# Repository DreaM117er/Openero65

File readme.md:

# OpeNero65

## 一、開發者前言

OpeNero65是我設計的第一把`ANSI配列`鍵盤，使用市面上都能輕易買到的RP2040開發板驅動，支援`QMK`/`VIAL`、多配列支持、階梯CapsLock等。本以為標準鍵盤外殼很好設計，後來發現單件CNC的價格過高，才改用堆疊外殼的設計方式，本次成品會採用3mm厚度壓克力製成。

OpeNero65 is the first `ANSI keyboard` I designed, it is driven by the RP2040 development board which can be easily purchased in the market, and it supports `QMK`/`VIAL`, multi-compatibility support, and ladder CapsLock, etc. Originally, I thought the standard keyboard case is very easy to design, then I found that the price of a single CNC is too high, so I switched to the stacked case design. Originally thought the standard keyboard case is very good design, but later found that the price of a single piece of CNC is too high, and then changed to the stacked case design, the finished product will be made of 3mm thickness acrylic.

設計堆疊殼也相當不輕鬆，特別是PCB階段它有一端是向外突起，接著開發板採用的是排針焊接固定，大大增加堆疊外殼的3D設計困難。仰角以堆疊外殼來說仰角有2種設計方式，但因為開發板固定在PCB上會有立體干涉存在，只能採用橫向堆疊的方式設計... 總體來說也經過一段時間折騰才順利完成。

The design of the stacked case is not easy, especially at the PCB stage it has an end that protrudes outward, and then the development board is fixed with rows of pins, which greatly increases the difficulty of the 3D design of the stacked case. Elevation angle to stack the case of the elevation angle of two design methods, but because the development board fixed on the PCB will have three-dimensional interference exists, can only be used in a horizontal stacking design... Overall, also after a period of time to successfully complete.

## 二、設計圖預覽

|||
|---|---|
|||
|||
|||

## 三、材料及使用工具

### A、材料：

|名稱|數量|備註|
|---|---|---|
|OpeNero65電路板（`PCB`）|1片|-|
|堆疊外殼（Stacking Case）|1組|10片堆疊材料|
|微控制器（`MCU`）|1片|`RP2040Supermini`、`RP2040Zero`|
|公母圓排針（M/F Pin header）|`9pin`、`5pin`|選配（`Optional`）|
|熱插拔座（Hotswap Sockets）|72個|`MX`規格（for MX switches）|
|`M2x5mm` 扁頭螺絲（Screws）|30根|-|
|`M2x4mm` 扁頭螺絲（Screws）|8根|-|
|`M2x3mm` 扁頭螺絲（Screws）|20根|-|
|`M2x18mm` 雙通銅柱（Spacer）|2根|-|
|`M2x12mm` 雙通銅柱（Spacer）|10根|-|
|`M2x5mm` 雙通銅柱（Spacer）|11根|-|
|`M2x3mm` 雙通銅柱（Spacer）|8根|-|
|`PCB`衛星軸（Stablizers）|3+1組|`2u`、`6.25u`/`7u`|
|衛星軸用潤滑酯|-|`Permatex 22058`/`81150`或`XHT-BDZ`|
|防滑腳貼（Rubber feets）|5個|高度隨個人而定|
|外徑`5mm` 內徑`2mm` 橡膠圈（Outer `ø5mm`, inner `ø2mm` O-rings）|15個|選配（`Optional`）|
|`M2` 防滑墊片（`M2` washers）|5個|選配（`Optional`）|

### B、使用工具：

- 電烙鐵及相關工具組（Solder gun and other packs）。
- 精密螺絲起子組（Screwdriver set）。
- 防靜電金屬鑷子（Anti-static metal tweezers）。
- 拔鍵器（Keycaps puller）。
- 拔軸器（Keyswitch puller）。
- 細毛毛刷（Brushes for stablizers）。

### C、注意事項：

> **Warning**
>
> 使用電烙鐵時注意用電、用火安全，環境通風。
> 
> Be carefull on fire and electricity safety when soldering in environmental ventilation.

> **Warning**
>
> 定製外殼前務必瞭解自身需求的鍵盤佈局（例如6.25u、7.00u Spacebar；WK、WKL等）。
> 
> Please understood which keyboard layout you need before making/ordering case. (ex: 6.25u, 7.00u spacebar; WK, WKL...)

> **Warning**
>
> 在定製製作Openero65外殼之前一定要特別注意，壓克力板一定會有`0.1-0.35mm`左右的公差存在，成品會比實際用計算機計算來的小一些。
> 
> Before you oeder cases from factory, arcylic boards must exist tolerances about `0.1-0.35mm`, the finished product will be smaller than the actual calculator.

> **Warning**
>
> 請準備個人喜歡的MX鍵軸65-66顆，以及調整衛星軸鋼絲的前置動作。
> 
> Please prepare 65-66 personal MX switches and adjusted stablizer wires before building keyboard.

材料及工具準備好之後，點我前往[組裝說明](guide.md)。

## 四、參考及使用資料
- [QMK Firmware](https://qmk.fm/).
- [VIAL](https://get.vial.today/).
- [KiCAD](https://www.kicad.org/) version `7.0.5.`
- [JLCPCB](https://jlcpcb.com/).
- [DeepL](https://www.deepl.com/translator).
- [AutoDesk Fusion360](https://www.autodesk.com/products/fusion-360/free-trial).
- Taiwan [Tatung University](https://www.ttu.edu.tw/) - [Department of Mechanical and Materials Engineering](https://mme.ttu.edu.tw/)
- And my friend: [YCT](https://github.com/yct38)

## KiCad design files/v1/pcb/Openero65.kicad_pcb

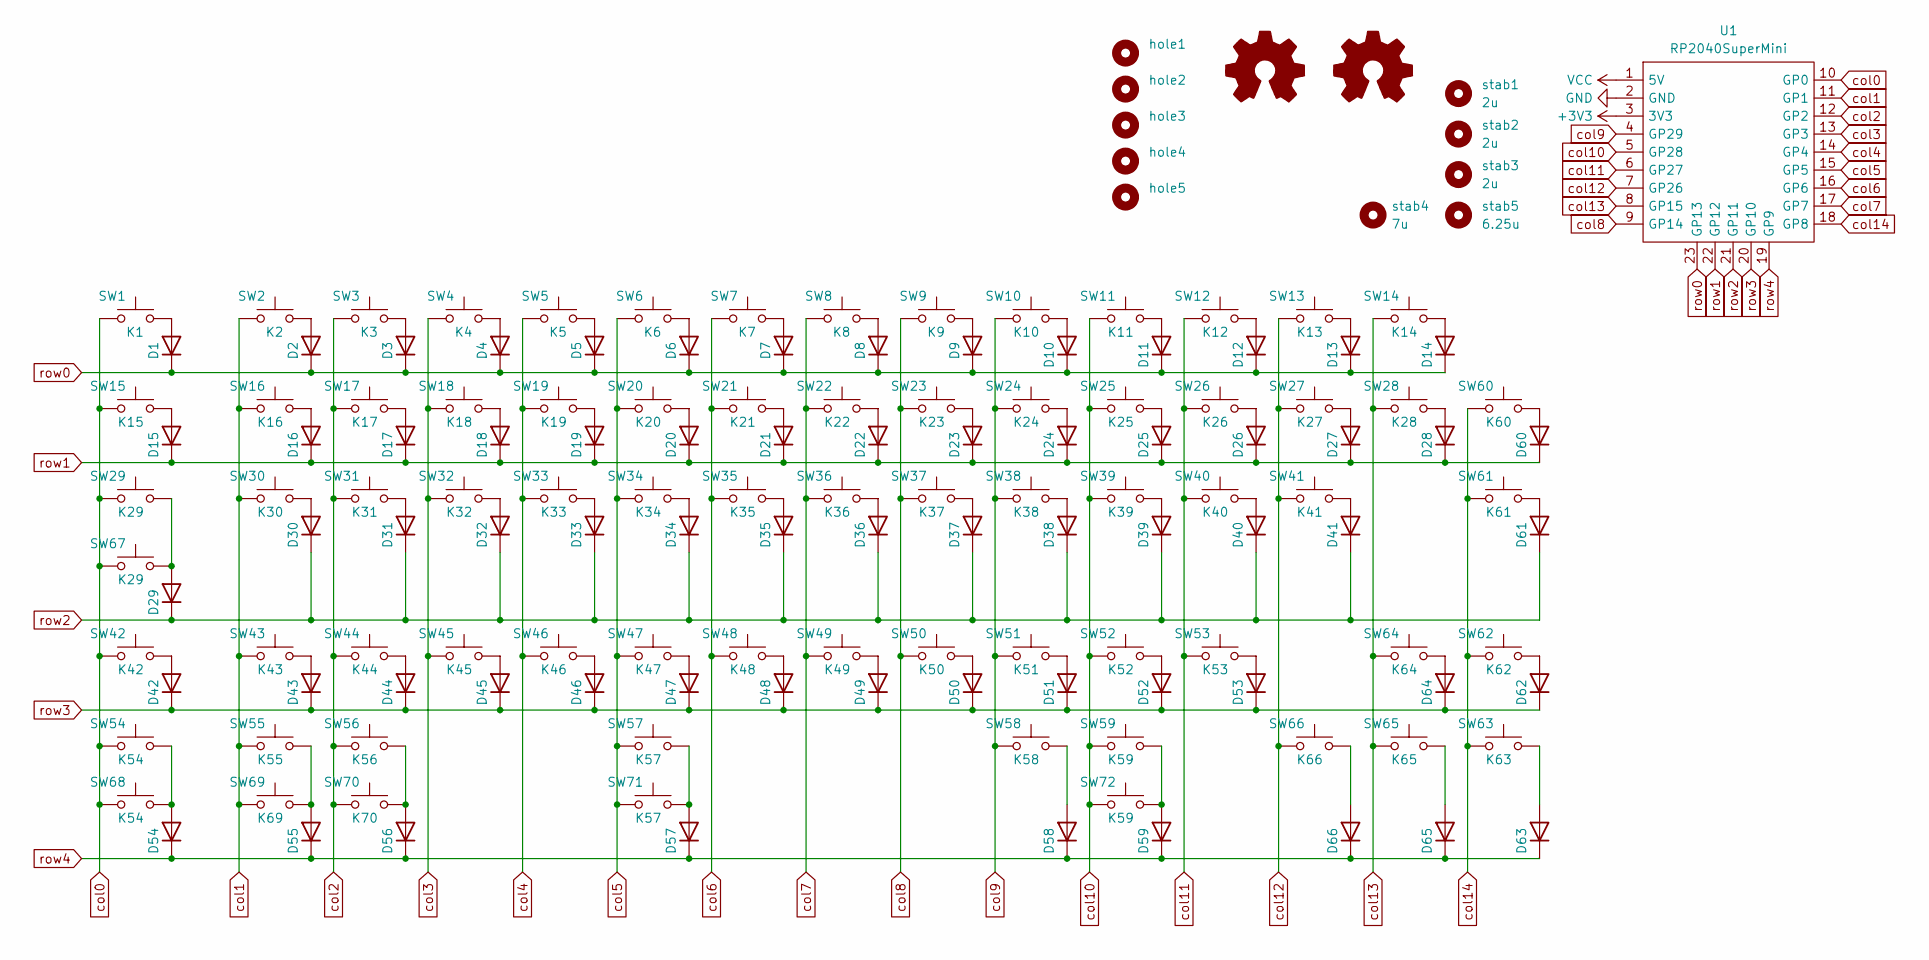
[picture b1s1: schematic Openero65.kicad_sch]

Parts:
D1, D2, D3, D4, D5, D6, D7, D8, D9, D10, D11, D12, D13, D14, D15, D16, D17, D18, D19, D20, D21, D22, D23, D24, D25, D26, D27, D28, D29, D30, D31, D32, D33, D34, D35, D36, D37, D38, D39, D40, D41, D42, D43, D44, D45, D46, D47, D48, D49, D50, D51, D52, D53, D54, D55, D56, D57, D58, D59, D60, D61, D62, D63, D64, D65, D66: 1N4148; D_SOD-123
SW1: K1; SW_Hotswap_Kailh_MX_Plated_1.00u
SW2: K2; SW_Hotswap_Kailh_MX_Plated_1.00u
SW3: K3; SW_Hotswap_Kailh_MX_Plated_1.00u
SW4: K4; SW_Hotswap_Kailh_MX_Plated_1.00u
SW5: K5; SW_Hotswap_Kailh_MX_Plated_1.00u
SW6: K6; SW_Hotswap_Kailh_MX_Plated_1.00u
SW7: K7; SW_Hotswap_Kailh_MX_Plated_1.00u
SW8: K8; SW_Hotswap_Kailh_MX_Plated_1.00u
SW9: K9; SW_Hotswap_Kailh_MX_Plated_1.00u
SW10: K10; SW_Hotswap_Kailh_MX_Plated_1.00u
SW11: K11; SW_Hotswap_Kailh_MX_Plated_1.00u
SW12: K12; SW_Hotswap_Kailh_MX_Plated_1.00u
SW13: K13; SW_Hotswap_Kailh_MX_Plated_1.00u
SW14: K14; SW_Hotswap_Kailh_MX_Plated_2.00u
SW15: K15; SW_Hotswap_Kailh_MX_Plated_1.50u
SW16: K16; SW_Hotswap_Kailh_MX_Plated_1.00u
SW17: K17; SW_Hotswap_Kailh_MX_Plated_1.00u
SW18: K18; SW_Hotswap_Kailh_MX_Plated_1.00u
SW19: K19; SW_Hotswap_Kailh_MX_Plated_1.00u
SW20: K20; SW_Hotswap_Kailh_MX_Plated_1.00u
SW21: K21; SW_Hotswap_Kailh_MX_Plated_1.00u
SW22: K22; SW_Hotswap_Kailh_MX_Plated_1.00u
SW23: K23; SW_Hotswap_Kailh_MX_Plated_1.00u
SW24: K24; SW_Hotswap_Kailh_MX_Plated_1.00u
SW25: K25; SW_Hotswap_Kailh_MX_Plated_1.00u
SW26: K26; SW_Hotswap_Kailh_MX_Plated_1.00u
SW27: K27; SW_Hotswap_Kailh_MX_Plated_1.00u
SW28: K28; SW_Hotswap_Kailh_MX_Plated_1.50u
SW29: K29; SW_Hotswap_Kailh_MX_Plated_1.75u
SW30: K30; SW_Hotswap_Kailh_MX_Plated_1.00u
SW31: K31; SW_Hotswap_Kailh_MX_Plated_1.00u
SW32: K32; SW_Hotswap_Kailh_MX_Plated_1.00u
SW33: K33; SW_Hotswap_Kailh_MX_Plated_1.00u
SW34: K34; SW_Hotswap_Kailh_MX_Plated_1.00u
SW35: K35; SW_Hotswap_Kailh_MX_Plated_1.00u
SW36: K36; SW_Hotswap_Kailh_MX_Plated_1.00u
SW37: K37; SW_Hotswap_Kailh_MX_Plated_1.00u
SW38: K38; SW_Hotswap_Kailh_MX_Plated_1.00u
SW39: K39; SW_Hotswap_Kailh_MX_Plated_1.00u
SW40: K40; SW_Hotswap_Kailh_MX_Plated_1.00u
SW41: K41; SW_Hotswap_Kailh_MX_Plated_2.25u
SW42: K42; SW_Hotswap_Kailh_MX_Plated_2.25u
SW43: K43; SW_Hotswap_Kailh_MX_Plated_1.00u
SW44: K44; SW_Hotswap_Kailh_MX_Plated_1.00u
SW45: K45; SW_Hotswap_Kailh_MX_Plated_1.00u
SW46: K46; SW_Hotswap_Kailh_MX_Plated_1.00u
SW47: K47; SW_Hotswap_Kailh_MX_Plated_1.00u
SW48: K48; SW_Hotswap_Kailh_MX_Plated_1.00u
SW49: K49; SW_Hotswap_Kailh_MX_Plated_1.00u
SW50: K50; SW_Hotswap_Kailh_MX_Plated_1.00u
SW51: K51; SW_Hotswap_Kailh_MX_Plated_1.00u
SW52: K52; SW_Hotswap_Kailh_MX_Plated_1.00u
SW53: K53; SW_Hotswap_Kailh_MX_Plated_1.75u
SW54: K54; SW_Hotswap_Kailh_MX_Plated_1.25u
SW55: K55; SW_Hotswap_Kailh_MX_Plated_1.25u
SW56: K56; SW_Hotswap_Kailh_MX_Plated_1.25u
SW57: K57; SW_Hotswap_Kailh_MX_Plated_6.25u
SW58: K58; SW_Hotswap_Kailh_MX_Plated_1.25u
SW59: K59; SW_Hotswap_Kailh_MX_Plated_1.25u
SW60: K60; SW_Hotswap_Kailh_MX_Plated_1.00u
SW61: K61; SW_Hotswap_Kailh_MX_Plated_1.00u
SW62: K62; SW_Hotswap_Kailh_MX_Plated_1.00u
SW63: K63; SW_Hotswap_Kailh_MX_Plated_1.00u
SW64: K64; SW_Hotswap_Kailh_MX_Plated_1.00u
SW65: K65; SW_Hotswap_Kailh_MX_Plated_1.00u
SW66: K66; SW_Hotswap_Kailh_MX_Plated_1.00u
SW67: K29; SW_Hotswap_Kailh_MX_Plated_1.25u
SW68: K54; SW_Hotswap_Kailh_MX_Plated_1.50u
SW69: K69; SW_Hotswap_Kailh_MX_Plated_1.00u
SW70: K70; SW_Hotswap_Kailh_MX_Plated_1.50u
SW71: K57; SW_Hotswap_Kailh_MX_Plated_7.00u
SW72: K59; SW_Hotswap_Kailh_MX_Plated_1.50u
U1: RP2040SuperMini; MCU_RP2040SuperMini
hole1, hole2, hole3, hole4, hole5: MountingHole_3.5mm
stab1, stab2, stab3: 2u; Stabilizer_Cherry_MX_2.00u
stab4: 7u; Stabilizer_Cherry_MX_7.00u
stab5: 6.25u; Stabilizer_Cherry_MX_6.25u

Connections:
+3V3: U1.3 (3V3)
GND: U1.2 (GND)
unnamed: D1.2 (A), SW1.2
unnamed: D2.2 (A), SW2.2
unnamed: D3.2 (A), SW3.2
unnamed: D4.2 (A), SW4.2
unnamed: D5.2 (A), SW5.2
unnamed: D6.2 (A), SW6.2
unnamed: D7.2 (A), SW7.2
unnamed: D8.2 (A), SW8.2
unnamed: D9.2 (A), SW9.2
unnamed: D10.2 (A), SW10.2
unnamed: D11.2 (A), SW11.2
unnamed: D12.2 (A), SW12.2
unnamed: D13.2 (A), SW13.2
unnamed: D14.2 (A), SW14.2
unnamed: D15.2 (A), SW15.2
unnamed: D16.2 (A), SW16.2
unnamed: D17.2 (A), SW17.2
unnamed: D18.2 (A), SW18.2
unnamed: D19.2 (A), SW19.2
unnamed: D20.2 (A), SW20.2
unnamed: D21.2 (A), SW21.2
unnamed: D22.2 (A), SW22.2
unnamed: D23.2 (A), SW23.2
unnamed: D24.2 (A), SW24.2
unnamed: D25.2 (A), SW25.2
unnamed: D26.2 (A), SW26.2
unnamed: D27.2 (A), SW27.2
unnamed: D28.2 (A), SW28.2
unnamed: D29.2 (A), SW29.2, SW67.2
unnamed: D30.2 (A), SW30.2
unnamed: D31.2 (A), SW31.2
unnamed: D32.2 (A), SW32.2
unnamed: D33.2 (A), SW33.2
unnamed: D34.2 (A), SW34.2
unnamed: D35.2 (A), SW35.2
unnamed: D36.2 (A), SW36.2
unnamed: D37.2 (A), SW37.2
unnamed: D38.2 (A), SW38.2
unnamed: D39.2 (A), SW39.2
unnamed: D40.2 (A), SW40.2
unnamed: D41.2 (A), SW41.2
unnamed: D42.2 (A), SW42.2
unnamed: D43.2 (A), SW43.2
unnamed: D44.2 (A), SW44.2
unnamed: D45.2 (A), SW45.2
unnamed: D46.2 (A), SW46.2
unnamed: D47.2 (A), SW47.2
unnamed: D48.2 (A), SW48.2
unnamed: D49.2 (A), SW49.2
unnamed: D50.2 (A), SW50.2
unnamed: D51.2 (A), SW51.2
unnamed: D52.2 (A), SW52.2
unnamed: D53.2 (A), SW53.2
unnamed: D54.2 (A), SW54.2, SW68.2
unnamed: D55.2 (A), SW55.2, SW69.2
unnamed: D56.2 (A), SW56.2, SW70.2
unnamed: D57.2 (A), SW57.2, SW71.2
unnamed: D58.2 (A), SW58.2
unnamed: D59.2 (A), SW59.2, SW72.2
unnamed: D60.2 (A), SW60.2
unnamed: D61.2 (A), SW61.2
unnamed: D62.2 (A), SW62.2
unnamed: D63.2 (A), SW63.2
unnamed: D64.2 (A), SW64.2
unnamed: D65.2 (A), SW65.2
unnamed: D66.2 (A), SW66.2
VCC: U1.1 (5V)
col0: SW1.1, SW15.1, SW29.1, SW42.1, SW54.1, SW67.1, SW68.1, U1.10 (GP0)
col1: SW2.1, SW16.1, SW30.1, SW43.1, SW55.1, SW69.1, U1.11 (GP1)
col2: SW3.1, SW17.1, SW31.1, SW44.1, SW56.1, SW70.1, U1.12 (GP2)
col3: SW4.1, SW18.1, SW32.1, SW45.1, U1.13 (GP3)
col4: SW5.1, SW19.1, SW33.1, SW46.1, U1.14 (GP4)
col5: SW6.1, SW20.1, SW34.1, SW47.1, SW57.1, SW71.1, U1.15 (GP5)
col6: SW7.1, SW21.1, SW35.1, SW48.1, U1.16 (GP6)
col7: SW8.1, SW22.1, SW36.1, SW49.1, U1.17 (GP7)
col8: SW9.1, SW23.1, SW37.1, SW50.1, U1.9 (GP14)
col9: SW10.1, SW24.1, SW38.1, SW51.1, SW58.1, U1.4 (GP29)
col10: SW11.1, SW25.1, SW39.1, SW52.1, SW59.1, SW72.1, U1.5 (GP28)
col11: SW12.1, SW26.1, SW40.1, SW53.1, U1.6 (GP27)
col12: SW13.1, SW27.1, SW41.1, SW66.1, U1.7 (GP26)
col13: SW14.1, SW28.1, SW64.1, SW65.1, U1.8 (GP15)
col14: SW60.1, SW61.1, SW62.1, SW63.1, U1.18 (GP8)
row0: D1.1 (K), D2.1 (K), D3.1 (K), D4.1 (K), D5.1 (K), D6.1 (K), D7.1 (K), D8.1 (K), D9.1 (K), D10.1 (K), D11.1 (K), D12.1 (K), D13.1 (K), D14.1 (K), U1.23 (GP13)
row1: D15.1 (K), D16.1 (K), D17.1 (K), D18.1 (K), D19.1 (K), D20.1 (K), D21.1 (K), D22.1 (K), D23.1 (K), D24.1 (K), D25.1 (K), D26.1 (K), D27.1 (K), D28.1 (K), D60.1 (K), U1.22 (GP12)
row2: D29.1 (K), D30.1 (K), D31.1 (K), D32.1 (K), D33.1 (K), D34.1 (K), D35.1 (K), D36.1 (K), D37.1 (K), D38.1 (K), D39.1 (K), D40.1 (K), D41.1 (K), D61.1 (K), U1.21 (GP11)
row3: D42.1 (K), D43.1 (K), D44.1 (K), D45.1 (K), D46.1 (K), D47.1 (K), D48.1 (K), D49.1 (K), D50.1 (K), D51.1 (K), D52.1 (K), D53.1 (K), D62.1 (K), D64.1 (K), U1.20 (GP10)
row4: D54.1 (K), D55.1 (K), D56.1 (K), D57.1 (K), D58.1 (K), D59.1 (K), D63.1 (K), D65.1 (K), D66.1 (K), U1.19 (GP9)

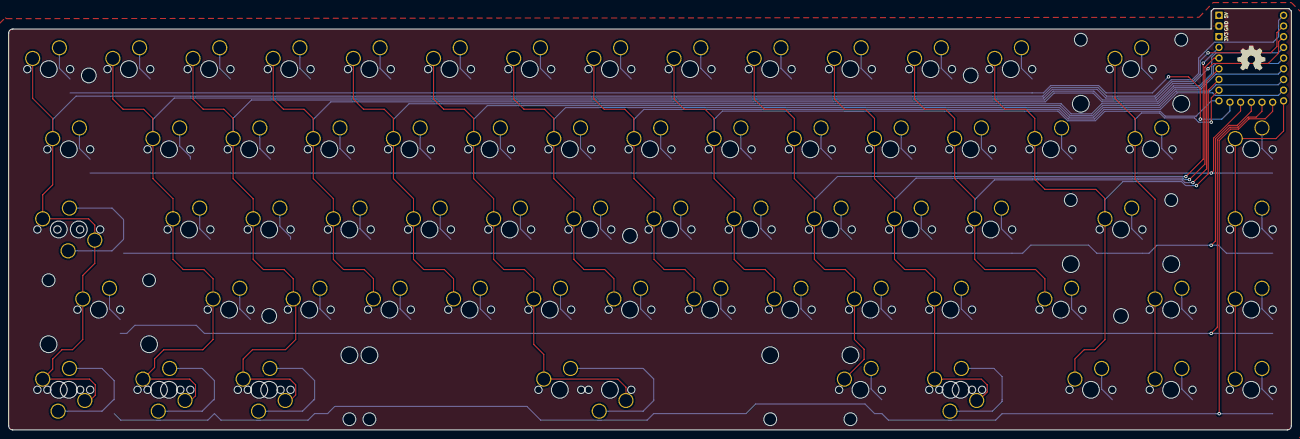
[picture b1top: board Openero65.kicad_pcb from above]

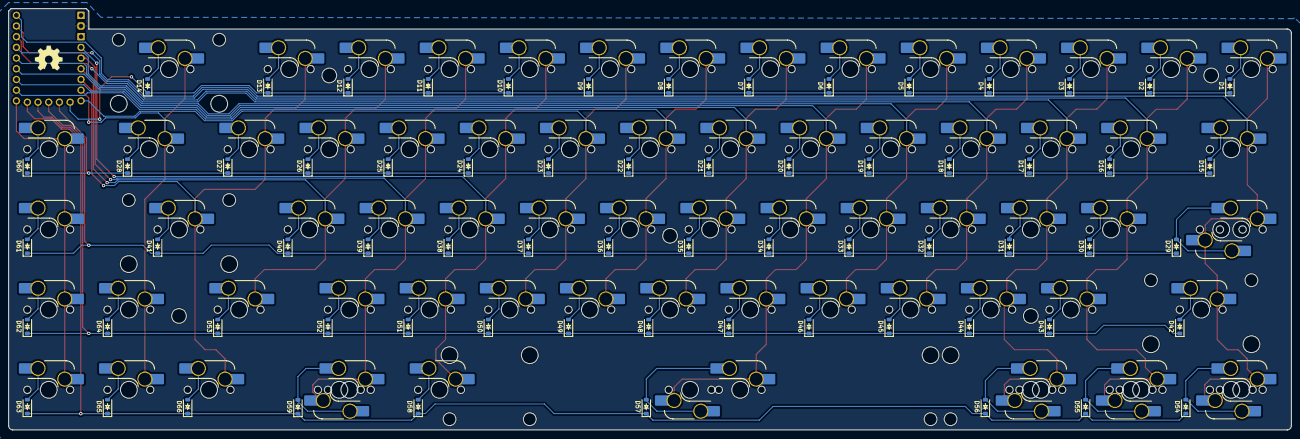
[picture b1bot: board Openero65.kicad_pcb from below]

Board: 2 copper layers, 304.8 x 100.1 mm, 149 parts (66 on the bottom side), 86 nets.

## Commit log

2023-11-15 update v1
2023-11-16 fix case 2
2023-11-17 fix case 1&2
2023-11-18 fix plate
2023-11-18 move plate.step
2023-11-19 fix usb-c cable outer hole
2023-11-19 Create LICENSE
2023-11-19 fix files on the z
2023-11-23 add wkl case
2023-11-30 fix case
2023-11-30 fix case and usb port
2023-12-01 change index picture
2023-12-05 fix wk case
2023-12-05 fix item list
2023-12-11 fix wkl case
2023-12-20 fix case 3
2023-12-25 update guide pics
